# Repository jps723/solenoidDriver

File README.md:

# Solenoid Driver Build Notes 1/26/20

This project is in partnership with [Bantam Tools](https://www.bantamtools.com)

**Design Notes:**

Each 12v solenoid has a 1N4001 diode in parallel with its positive/negative leads, serving as a flyback diode.  The TIP120s serve as switches with signals being directed via an external microcontroller through a 2.2k resistor.

The board is broken up into two sides, with the Arduino signals coming in on one side, and the solenoids being actuated on the other, indicated by an A (Arduino) and an S (Solenoid) in each of the two rows.  External power (12v) enters through a screw terminal on the side of the board.  Polarity is indicated with +/- symbols next to the screw terminals where applicable.  Solenoids are non-polar and so can be oriented any way.  Each Arduino screw terminal port is identical with the exception of one which is required for ground (as indicated by a ‘-‘ symbol).  Arduino signal pins can be any digital pin.

# Build Process
**Bit:** 1/32”
**Mill Time:** <10mins

It’s easiest to solder in this order:
```
1. Resistors
2. Diodes
3. Screw Terminals
4. TIP120s
5. Install heatsinks
```

Test - Sample Code (also within directory)

```
int solenoidPins[] = { 9, 10, 11, 12, 13 };
void setup() {
  setupPins(solenoidPins, 5);
}
void loop() {
  for (int i = 0; i < 5; i++) {
    digitalWrite(solenoidPins[i], HIGH);
	delay(80);
    digitalWrite(solenoidPins[i], LOW);
	delay(80);
  }
}
//set the pins as outputs
void setupPins(int pins[], int lengthOfArray) {
  for (int i = 0; i < lengthOfArray; i++) {
	pinMode(pins[i], OUTPUT);
  }
}
```

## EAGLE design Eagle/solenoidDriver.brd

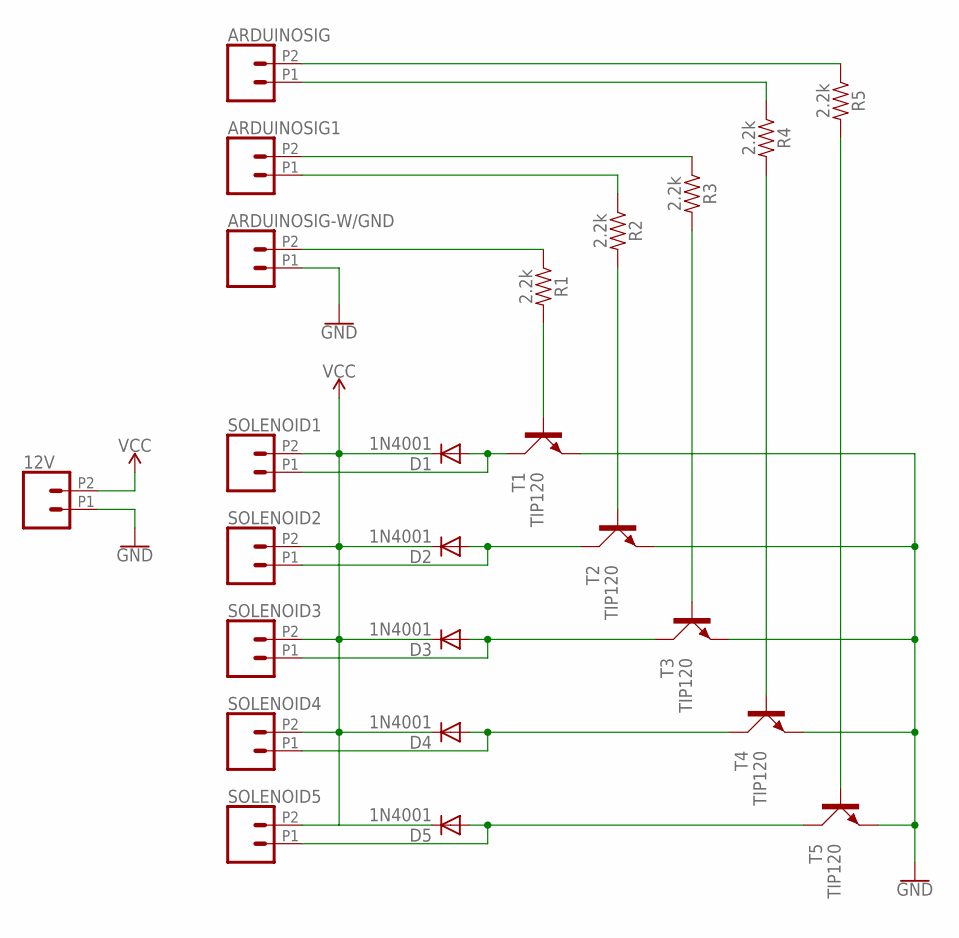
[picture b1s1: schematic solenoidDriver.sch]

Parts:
12V: CONN_022.54MM_SCREWTERM; 1X02_2.54_SCREWTERM
ARDUINOSIG, ARDUINOSIG1: CONN_022.54MM_SCREWTERM; 1X02_2.54_SCREWTERM
ARDUINOSIG-W/GND: CONN_022.54MM_SCREWTERM; 1X02_2.54_SCREWTERM
D1, D2, D3, D4, D5: 1N4001; DO41-10
R1, R2, R3, R4, R5: 2.2k; AXIAL-0.3-KIT
SOLENOID1, SOLENOID2, SOLENOID3, SOLENOID4, SOLENOID5: CONN_022.54MM_SCREWTERM; 1X02_2.54_SCREWTERM
T1, T2, T3, T4, T5: TIP120; TO220AH-NOHOLE

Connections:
GND: 12V.P1 (1), ARDUINOSIG-W/GND.P1 (1), T1.E, T2.E, T3.E, T4.E, T5.E
unnamed: R1.P$2 (2), T1.B
unnamed: ARDUINOSIG-W/GND.P2 (2), R1.P$1 (1)
unnamed: ARDUINOSIG.P2 (2), R5.P$1 (1)
unnamed: R5.P$2 (2), T5.B
unnamed: ARDUINOSIG.P1 (1), R4.P$1 (1)
unnamed: R4.P$2 (2), T4.B
unnamed: ARDUINOSIG1.P2 (2), R3.P$1 (1)
unnamed: R3.P$2 (2), T3.B
unnamed: ARDUINOSIG1.P1 (1), R2.P$1 (1)
unnamed: R2.P$2 (2), T2.B
unnamed: D2.A, SOLENOID2.P1 (1), T2.C
unnamed: D1.A, SOLENOID1.P1 (1), T1.C
unnamed: D4.A, SOLENOID4.P1 (1), T4.C
unnamed: D3.A, SOLENOID3.P1 (1), T3.C
unnamed: D5.A, SOLENOID5.P1 (1), T5.C
VCC: 12V.P2 (2), D1.C, D2.C, D3.C, D4.C, D5.C, SOLENOID1.P2 (2), SOLENOID2.P2 (2), SOLENOID3.P2 (2), SOLENOID4.P2 (2), SOLENOID5.P2 (2)

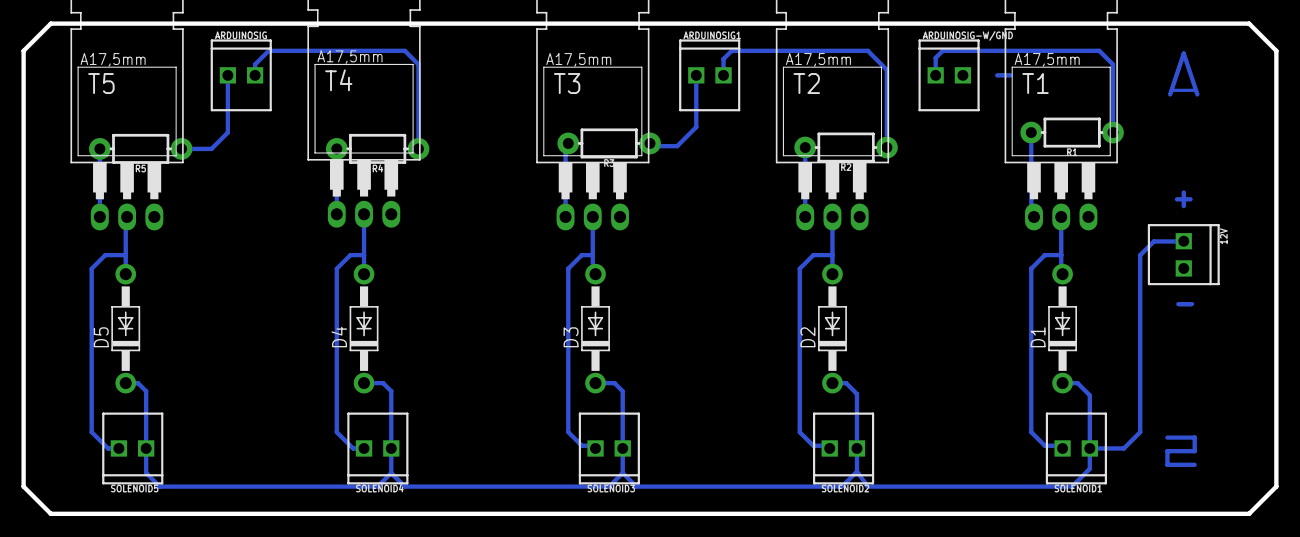
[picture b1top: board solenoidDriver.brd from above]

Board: 2 copper layers, 116.8 x 45.7 mm, 24 parts (0 on the bottom side), 17 nets.

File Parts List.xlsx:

Part | Quantity | Notes
Solenoids | 5.0 | 12v1a
TIP120 Transistors | 5.0
Screw Terminals | 9.0 | 1x2, .1" Pitch
2.2k Resistors | 5.0
1N4001 Diodes | 5.0

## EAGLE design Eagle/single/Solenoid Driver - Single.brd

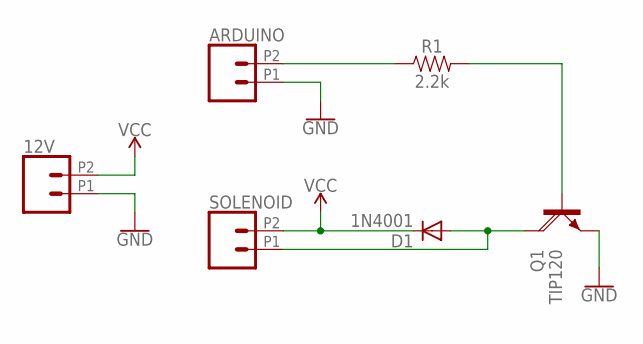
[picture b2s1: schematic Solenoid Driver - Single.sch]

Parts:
12V: CONN_022.54MM_SCREWTERM; 1X02_2.54_SCREWTERM
ARDUINO: CONN_022.54MM_SCREWTERM; 1X02_2.54_SCREWTERM
D1: 1N4001; DO41-10
Q1: TIP120; TO220AH
R1: 2.2k; AXIAL-0.3-KIT
SOLENOID: CONN_022.54MM_SCREWTERM; 1X02_2.54_SCREWTERM

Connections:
GND: 12V.P1 (1), ARDUINO.P1 (1), Q1.E
unnamed: Q1.B, R1.P$2 (2)
unnamed: ARDUINO.P2 (2), R1.P$1 (1)
unnamed: D1.A, Q1.C, SOLENOID.P1 (1)
VCC: 12V.P2 (2), D1.C, SOLENOID.P2 (2)

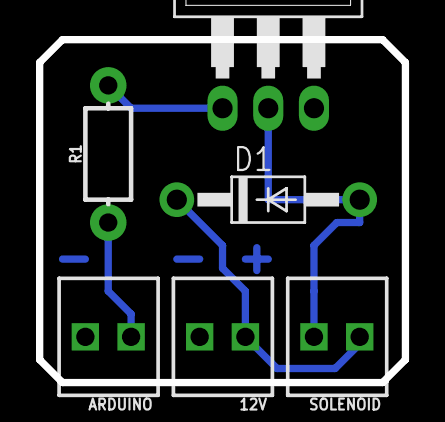
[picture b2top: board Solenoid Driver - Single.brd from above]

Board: 2 copper layers, 20.3 x 19.1 mm, 6 parts (0 on the bottom side), 5 nets.

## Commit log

2020-10-30 added bantam tools credit

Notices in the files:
parts and their libraries:
SparkFun-Connectors: Licensing: Creative Commons ShareAlike 4.0 International - https://creativecommons.org/licenses/by-sa/4.0
